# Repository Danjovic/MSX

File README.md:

# MSX
Coletânea de projetos para MSX

1) - Cartucho Caps Lock para Expert, descrito em http://danjovic.blogspot.com/2016/10/cartucho-caps-lock-para-expert.html

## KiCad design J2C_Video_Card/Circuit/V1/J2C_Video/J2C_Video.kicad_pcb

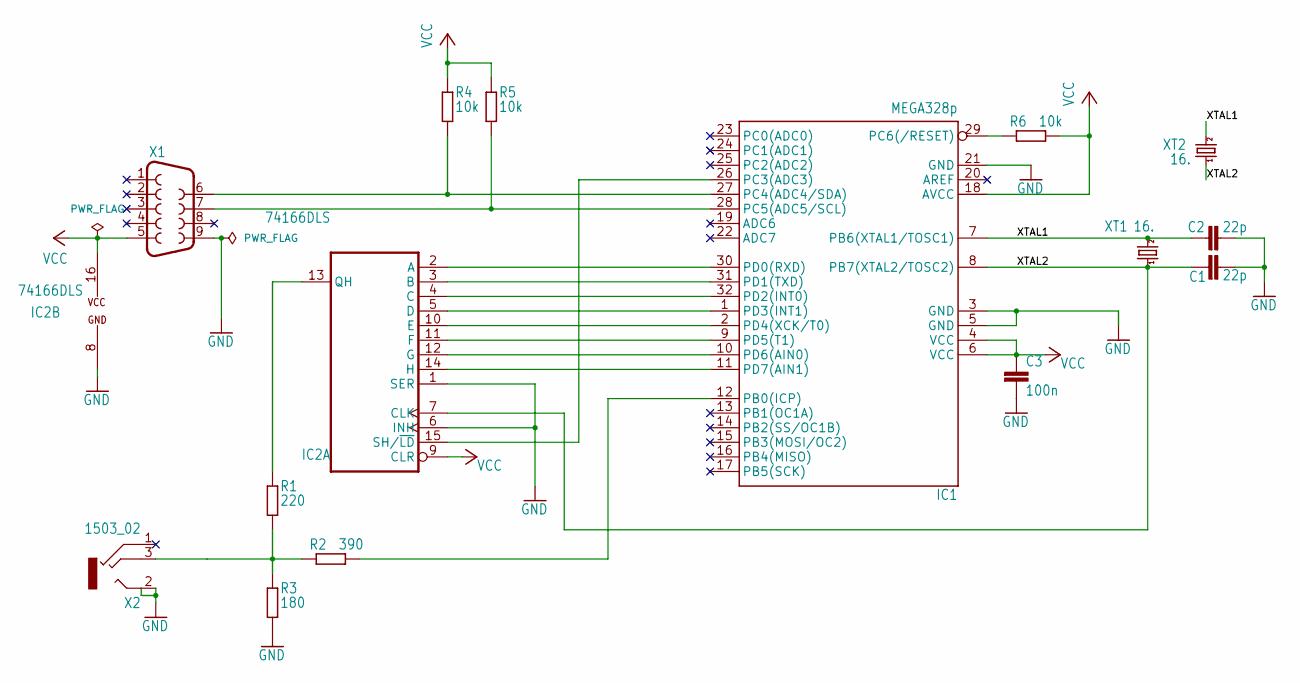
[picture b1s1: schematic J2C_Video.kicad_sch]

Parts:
C1, C2: 22p; C0805
C3: 100n; C0805
IC1: MEGA328p; TQFP32-08; MPN ATMEGA8-16AU
IC2: 74166DLS; SO16
R1: 220; M0805
R2: 390; M0805
R3: 180; M0805
R4, R5, R6: 10k; M0805
X1: F09D
X2: 1503_02
XT1: 16.; TC26V
XT2: 16.; Crystal_HC49-U_Vertical

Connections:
/XTAL1: C2.1, IC1.7 (PB6(XTAL1/TOSC1)), XT1.2, XT2.2
/XTAL2: C1.1, IC1.8 (PB7(XTAL2/TOSC2)), IC2.7 (CLK), XT1.1, XT2.1
GND: C1.2, C2.2, C3.2, IC1.3 (GND), IC1.5 (GND), IC1.21 (GND), IC2.1 (SER), IC2.6 (INH), IC2.8 (GND), R3.2, X1.9, X2.2, X2.2@2 (2)
unnamed: IC1.12 (PB0(ICP)), R2.2
unnamed: IC1.26 (PC3(ADC3)), IC2.15 (SH/~LD)
unnamed: IC1.27 (PC4(ADC4/SDA)), R4.2, X1.6
unnamed: IC1.28 (PC5(ADC5/SCL)), R5.2, X1.7
unnamed: IC1.29 (PC6(/RESET)), R6.1
unnamed: IC1.30 (PD0(RXD)), IC2.2 (A)
unnamed: IC1.31 (PD1(TXD)), IC2.3 (B)
unnamed: IC1.32 (PD2(INT0)), IC2.4 (C)
unnamed: IC1.1 (PD3(INT1)), IC2.5 (D)
unnamed: IC1.2 (PD4(XCK/T0)), IC2.10 (E)
unnamed: IC1.9 (PD5(T1)), IC2.11 (F)
unnamed: IC1.10 (PD6(AIN0)), IC2.12 (G)
unnamed: IC1.11 (PD7(AIN1)), IC2.14 (H)
unnamed: IC2.13 (QH), R1.2
unnamed: R1.1, R2.1, R3.1, X2.3
VCC: C3.1, IC1.4 (VCC), IC1.6 (VCC), IC1.18 (AVCC), IC2.9 (CLR), IC2.16 (VCC), R4.1, R5.1, R6.2, X1.5

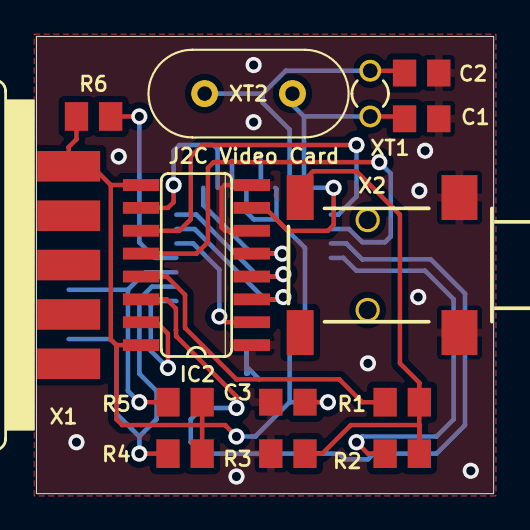
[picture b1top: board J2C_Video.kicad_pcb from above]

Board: 2 copper layers, 25.4 x 25.4 mm, 15 parts (1 on the bottom side), 19 nets.

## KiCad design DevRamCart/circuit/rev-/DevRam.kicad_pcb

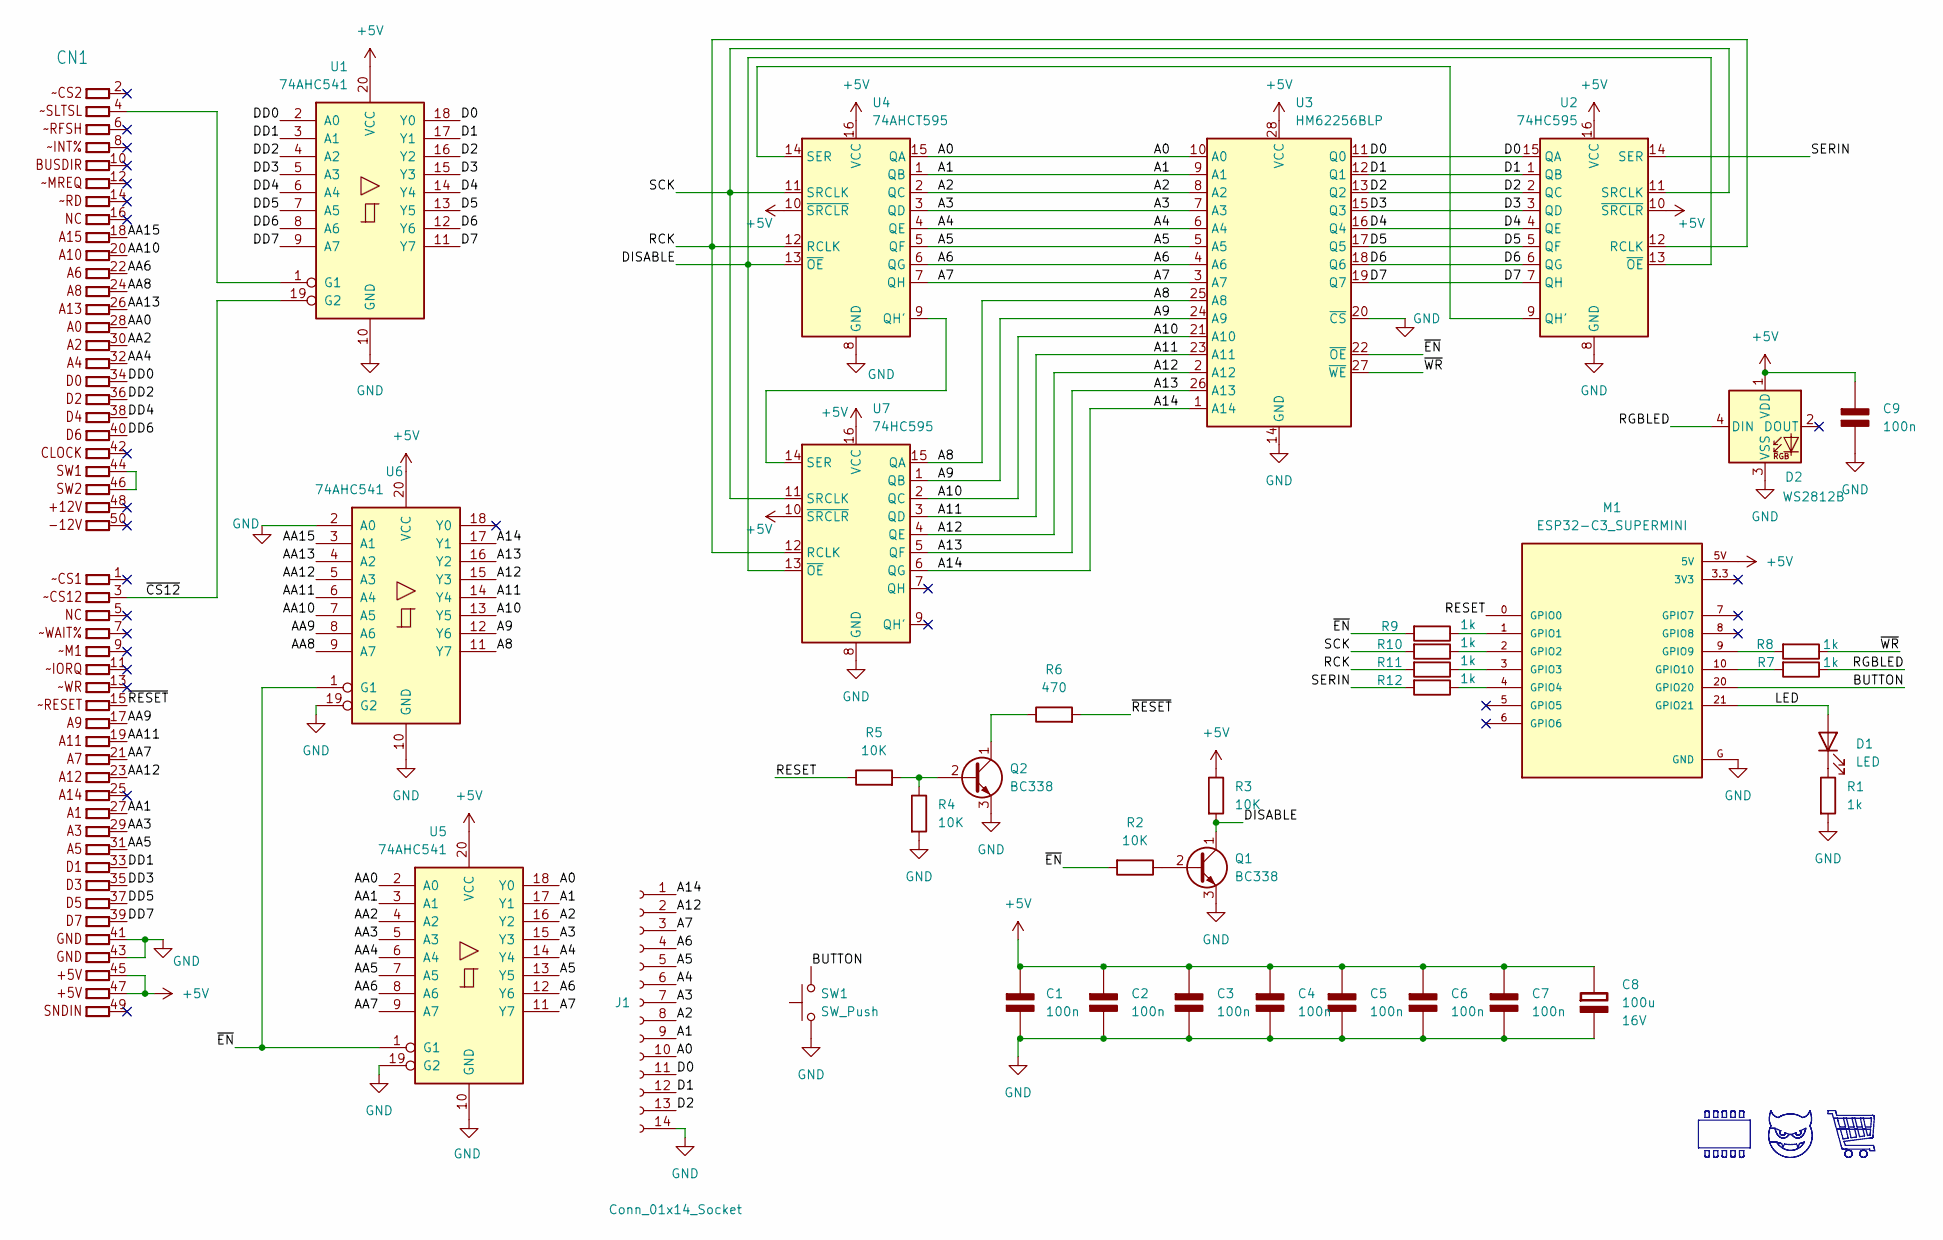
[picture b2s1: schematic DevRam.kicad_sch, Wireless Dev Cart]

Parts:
C1, C2, C3, C4, C5, C6, C7: 100n; C_Disc_D7.5mm_W2.5mm_P5.00mm; Rating V
C8: 100u; CP_Radial_D5.0mm_P2.50mm; Rating 16V
C9: 100n; C_0805_2012Metric; Rating V
CN1: MSXCART
D1: LED; LED_D3.0mm_Horizontal_O1.27mm_Z6.0mm
D2: WS2812B; LED_WS2812B_PLCC4_5.0x5.0mm_P3.2mm
J1: Conn_01x14_Socket; PinHeader_1x14_P2.54mm_Vertical
M1: ESP32-C3_SUPERMINI; MODULE_ESP32-C3_SUPERMINI
Q1, Q2: BC338; TO-92
R1: 1k; R_Axial_DIN0207_L6.3mm_D2.5mm_P7.62mm_Horizontal
R2, R3, R4, R5: 10K; R_Axial_DIN0207_L6.3mm_D2.5mm_P7.62mm_Horizontal
R6: 470; R_Axial_DIN0207_L6.3mm_D2.5mm_P7.62mm_Horizontal
R7, R8, R9, R10, R11, R12: 1k; R_0805_2012Metric
SW1: SW_Push; SW_SPST_Omron_B3F-315x_Angled
U1, U5, U6: 74AHC541; DIP-20_W7.62mm
U2, U7: 74HC595; DIP-16_W7.62mm
U3: HM62256BLP; DIP-28_W7.62mm
U4: 74AHCT595; DIP-16_W7.62mm

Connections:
+5V: C1.1 (+), C2.1 (+), C3.1 (+), C4.1 (+), C5.1 (+), C6.1 (+), C7.1 (+), C8.1 (+), C9.1 (+), CN1.45 (45.+5V), CN1.47 (47.+5V), D2.1 (VDD), M1.5V, R3.1, U1.20 (VCC), U2.10 (~SRCLR), U2.16 (VCC), U3.28 (VCC), U4.10 (~SRCLR), U4.16 (VCC), U5.20 (VCC), U6.20 (VCC), U7.10 (~SRCLR), U7.16 (VCC)
/A0: J1.10, U3.10 (A0), U4.15 (QA), U5.18 (Y0)
/A1: J1.9, U3.9 (A1), U4.1 (QB), U5.17 (Y1)
/A2: J1.8, U3.8 (A2), U4.2 (QC), U5.16 (Y2)
/A3: J1.7, U3.7 (A3), U4.3 (QD), U5.15 (Y3)
/A4: J1.6, U3.6 (A4), U4.4 (QE), U5.14 (Y4)
/A5: J1.5, U3.5 (A5), U4.5 (QF), U5.13 (Y5)
/A6: J1.4, U3.4 (A6), U4.6 (QG), U5.12 (Y6)
/A7: J1.3, U3.3 (A7), U4.7 (QH), U5.11 (Y7)
/A8: U3.25 (A8), U6.11 (Y7), U7.15 (QA)
/A9: U3.24 (A9), U6.12 (Y6), U7.1 (QB)
/A10: U3.21 (A10), U6.13 (Y5), U7.2 (QC)
/A11: U3.23 (A11), U6.14 (Y4), U7.3 (QD)
/A12: J1.2, U3.2 (A12), U6.15 (Y3), U7.4 (QE)
/A13: U3.26 (A13), U6.16 (Y2), U7.5 (QF)
/A14: J1.1, U3.1 (A14), U6.17 (Y1), U7.6 (QG)
/AA0: CN1.28 (28.A0), U5.2 (A0)
/AA1: CN1.27 (27.A1), U5.3 (A1)
/AA2: CN1.30 (30.A2), U5.4 (A2)
/AA3: CN1.29 (29.A3), U5.5 (A3)
/AA4: CN1.32 (32.A4), U5.6 (A4)
/AA5: CN1.31 (31.A5), U5.7 (A5)
/AA6: CN1.22 (22.A6), U5.8 (A6)
/AA7: CN1.21 (21.A7), U5.9 (A7)
/AA8: CN1.24 (24.A8), U6.9 (A7)
/AA9: CN1.17 (17.A9), U6.8 (A6)
/AA10: CN1.20 (20.A10), U6.7 (A5)
/AA11: CN1.19 (19.A11), U6.6 (A4)
/AA12: CN1.23 (23.A12), U6.5 (A3)
/AA13: CN1.26 (26.A13), U6.4 (A2)
/AA15: CN1.18 (18.A15), U6.3 (A1)
/BUTTON: M1.20 (GPIO20), SW1.2
/D0: J1.11, U1.18 (Y0), U2.15 (QA), U3.11 (Q0)
/D1: J1.12, U1.17 (Y1), U2.1 (QB), U3.12 (Q1)
/D2: J1.13, U1.16 (Y2), U2.2 (QC), U3.13 (Q2)
/D3: U1.15 (Y3), U2.3 (QD), U3.15 (Q3)
/D4: U1.14 (Y4), U2.4 (QE), U3.16 (Q4)
/D5: U1.13 (Y5), U2.5 (QF), U3.17 (Q5)
/D6: U1.12 (Y6), U2.6 (QG), U3.18 (Q6)
/D7: U1.11 (Y7), U2.7 (QH), U3.19 (Q7)
/DD0: CN1.34 (34.D0), U1.2 (A0)
/DD1: CN1.33 (33.D1), U1.3 (A1)
/DD2: CN1.36 (36.D2), U1.4 (A2)
/DD3: CN1.35 (35.D3), U1.5 (A3)
/DD4: CN1.38 (38.D4), U1.6 (A4)
/DD5: CN1.37 (37.D5), U1.7 (A5)
/DD6: CN1.40 (40.D6), U1.8 (A6)
/DD7: CN1.39 (39.D7), U1.9 (A7)
/DISABLE: Q1.1 (C), R3.2, U2.13 (~OE), U4.13 (~OE), U7.13 (~OE)
/LED: D1.2 (A), M1.21 (GPIO21)
/RCK: R11.2, U2.12 (RCLK), U4.12 (RCLK), U7.12 (RCLK)
/RESET: M1.0 (GPIO0), R5.1
/RGBLED: D2.4 (DIN), R7.1
/SCK: R10.2, U2.11 (SRCLK), U4.11 (SRCLK), U7.11 (SRCLK)
/SERIN: R12.2, U2.14 (SER)
/~CS12: CN1.3 (3.~CS12), U1.19 (G2)
/~EN: R2.2, R9.2, U3.22 (~OE), U5.1 (G1), U6.1 (G1)
/~RESET: CN1.15 (15.~RESET), R6.2
/~WR: R8.1, U3.27 (~WE)
GND: C1.2 (-), C2.2 (-), C3.2 (-), C4.2 (-), C5.2 (-), C6.2 (-), C7.2 (-), C8.2 (-), C9.2 (-), CN1.41 (41.GND), CN1.43 (43.GND), D2.3 (VSS), J1.14, M1.G (GND), Q1.3 (E), Q2.3 (E), R1.2, R4.2, SW1.1, U1.10 (GND), U2.8 (GND), U3.14 (GND), U3.20 (~CS), U4.8 (GND), U5.10 (GND), U5.19 (G2), U6.2 (A0), U6.10 (GND), U6.19 (G2), U7.8 (GND)
unnamed: CN1.4 (4.~SLTSL), U1.1 (G1)
unnamed: CN1.44 (44.SW1), CN1.46 (46.SW2)
unnamed: D1.1 (K), R1.1
unnamed: Q2.2 (B), R4.1, R5.2
unnamed: Q2.1 (C), R6.1
unnamed: Q1.2 (B), R2.1
unnamed: U4.9 (QH'), U7.14 (SER)
unnamed: U2.9 (QH'), U4.14 (SER)
unnamed: M1.1 (GPIO1), R9.1
unnamed: M1.2 (GPIO2), R10.1
unnamed: M1.3 (GPIO3), R11.1
unnamed: M1.4 (GPIO4), R12.1
unnamed: M1.9 (GPIO9), R8.2
unnamed: M1.10 (GPIO10), R7.2

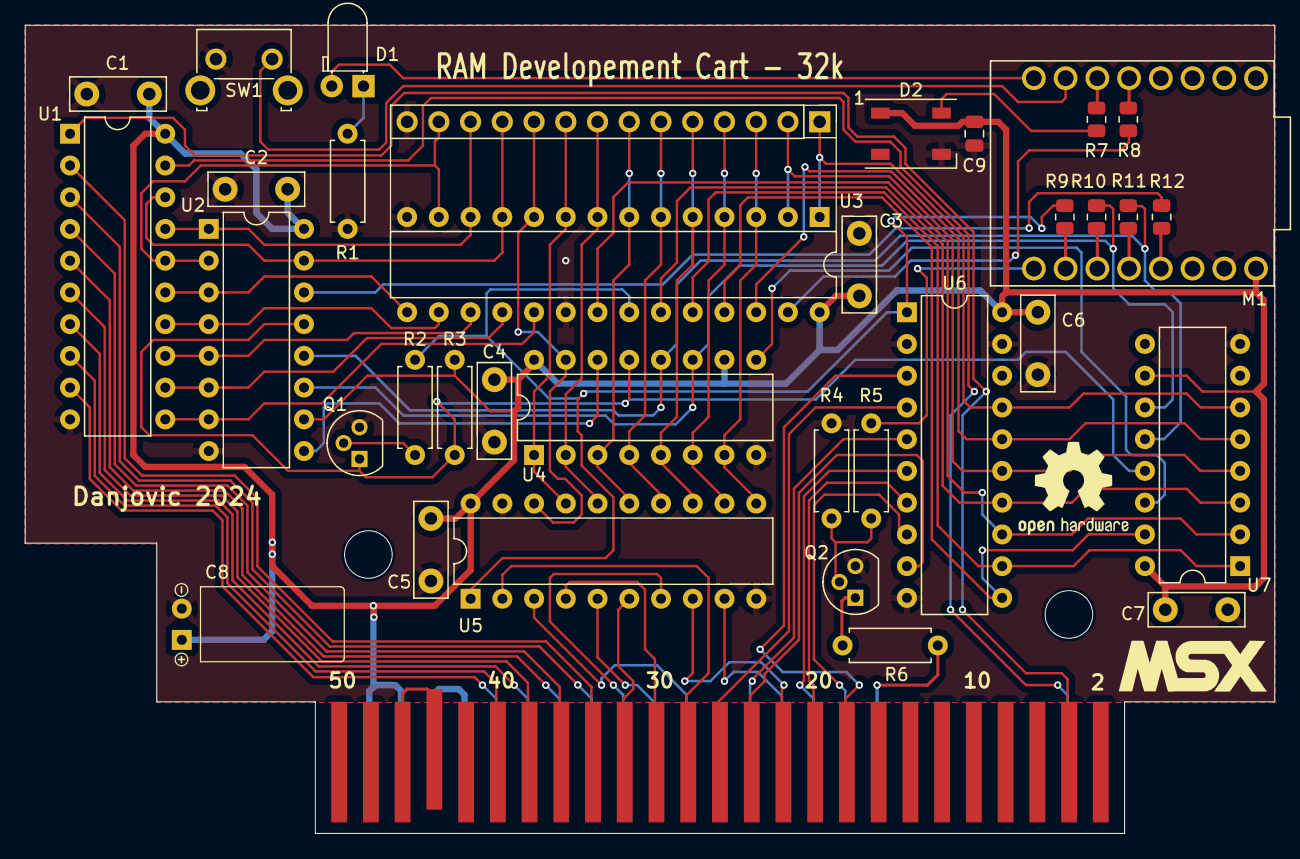
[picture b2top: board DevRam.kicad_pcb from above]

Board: 2 copper layers, 100.0 x 64.7 mm, 36 parts (0 on the bottom side), 74 nets.

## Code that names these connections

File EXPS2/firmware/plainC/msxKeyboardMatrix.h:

//    _____  _____  ___   _____
//   | __\ \/ / _ \/ __| / /_  )
//   | _| >  <|  _/\__ \/ / / /
//   |___/_/\_\_|  |___/_/ /___|
//
//   Teclado PS/2 externo para Expert XP800

// Conexao dos pinos do AVR com a PPI
// AVR interface pin assignment to the PPI

// AVR  PPI

// PC0  PC0   /   sel A
// PC1  PC1   /   sel B
// PC2  PC2   /   sel C
// PC3  PC3   /   sel D

// PD0  PB5   /   X5
// PD1  PB0   /   X0
// PD2  PB6   /   X6
// PD3  PB2   /   X2
// PD4  PB7   /   X7
// PD5  PB4   /   X4
// PD6  PB1   /   X1
// PD7  PB3   /   X3

/*
SH  ROW[0..10] COL [0..7]

    7     6     5     4     3     2     1     0    BIT
 +-----------------------------------------------+
 |SHIFT|       ROW [0..10]     |    COL[0..7]    |
 +-----------------------------------------------+


    7     6     5     4     3     2     1     0    BIT
 +-----------------------------------------------+
 |  7  |  5  |  6  |  4  |  3  |  2  |  1  |  0  |   Row 0
 +-----+-----+-----+-----+-----+-----+-----+-----|
 |  ;  |  [  |  ]  |  \  |  =  |  -  |  9  |  8  |   Row 1
 +-----+-----+-----+-----+-----+-----+-----+-----|
 |  B  |  |  |  A  |  /  |  .  |  ,  |  `  |  '  |   Row 2
 +-----+-----+-----+-----+-----+-----+-----+-----|
 |  J  |  H  |  I  |  G  |  F  |  E  |  D  |  C  |   Row 3
 +-----+-----+-----+-----+-----+-----+-----+-----|
 |  R  |  P  |  Q  |  O  |  N  |  M  |  L  |  K  |   Row 4
 +-----+-----+-----+-----+-----+-----+-----+-----|
 |  Z  |  X  |  Y  |  W  |  V  |  U  |  T  |  S  |   Row 5
 +-----+-----+-----+-----+-----+-----+-----+-----|
 | F3  | F1  | F2  |CODE | CAP |GRAPH|CTRL |SHIFT|   Row 6
 +-----+-----+-----+-----+-----+-----+-----+-----|
 | CR  | BS  | SEL |STOP | TAB | ESC | F5  | F4  |   Row 7
 +-----+-----+-----+-----+-----+-----+-----+-----|
 |RIGHT| UP  |DOWN |LEFT | DEL | INS |HOME |SPACE|   Row 8
 +-----+-----+-----+-----+-----+-----+-----+-----|
 | KP4 | KP2 | KP2 | KP1 | KP0 |NUM/ |NUM+ |NUM* |   Row 9
 +-----+-----+-----+-----+-----+-----+-----+-----|
 |  .  |  -  |  ,  | KP9 | KP8 | KP7 | KP6 | KP5 |   Row 10
 +-----------------------------------------------+
    7     5     6     4     3     2     1     0       Column

*/

// Mapa das linhas de selecao da PPI
// PPI selection line mapping
//      line bit
#define selA  0
#define selB  1
#define selC  2
#define selD  3


#define row0  ( (0<<selD)|(0<<selC)|(0<<selB)|(0<<selA) ) <<3
#define row1  ( (0<<selD)|(0<<selC)|(0<<selB)|(1<<selA) ) <<3
#define row2  ( (0<<selD)|(0<<selC)|(1<<selB)|(0<<selA) ) <<3
#define row3  ( (0<<selD)|(0<<selC)|(1<<selB)|(1<<selA) ) <<3
#define row4  ( (0<<selD)|(1<<selC)|(0<<selB)|(0<<selA) ) <<3
#define row5  ( (0<<selD)|(1<<selC)|(0<<selB)|(1<<selA) ) <<3
#define row6  ( (0<<selD)|(1<<selC)|(1<<selB)|(0<<selA) ) <<3
#define row7  ( (0<<selD)|(1<<selC)|(1<<selB)|(1<<selA) ) <<3
#define row8  ( (1<<selD)|(0<<selC)|(0<<selB)|(0<<selA) ) <<3
#define row9  ( (1<<selD)|(0<<selC)|(0<<selB)|(1<<selA) ) <<3
#define rowA  ( (1<<selD)|(0<<selC)|(1<<selB)|(0<<selA) ) <<3
#define rowB  ( (1<<selD)|(0<<selC)|(1<<selB)|(1<<selA) ) <<3
#define rowC  ( (1<<selD)|(1<<selC)|(0<<selB)|(0<<selA) ) <<3
#define rowD  ( (1<<selD)|(1<<selC)|(0<<selB)|(1<<selA) ) <<3
#define rowE  ( (1<<selD)|(1<<selC)|(1<<selB)|(0<<selA) ) <<3
#define rowF  ( (1<<selD)|(1<<selC)|(1<<selB)|(1<<selA) ) <<3


// Posicao das bits das colunas (teclas)
// Column position bit mapping (keys)
//   column  bit
#define col0  5
#define col1  0
#define col2  6
#define col3  2
#define col4  7
#define col5  4
#define col6  1
#define col7  3


//  SHIFT Position in Matrx
#define LIN_SHIFT 6
#define COL_SHIFT col0


#define _NONE          0x7F
#define _SH            0x80

#define _0            ( row0 | col0 )
#define _1            ( row0 | col1 )
#define _2            ( row0 | col2 )
#define _3            ( row0 | col3 )
#define _4            ( row0 | col4 )
#define _5            ( row0 | col5 )
#define _6            ( row0 | col6 )
#define _7            ( row0 | col7 )

#define _8            ( row1 | col0 )
#define _9            ( row1 | col1 )
#define _MINUS        ( row1 | col2 )
#define _EQUAL        ( row1 | col3 )
#define _OPENBRACKET  ( row1 | col4 )
#define _ACUTE        ( row1 | col5 )
#define _OPENKEY      ( row1 | col6 )
#define _TILDE        ( row1 | col7 )

#define _ASTERISK     ( row2 | col0 )
#define _CCEDIL       ( row2 | col1 )
#define _COMMA        ( row2 | col2 )
#define _DOT          ( row2 | col3 )
#define _SEMICOLON    ( row2 | col4 )
#define _SLASH        ( row2 | col5 )
#define _A            ( row2 | col6 )
#define _B            ( row2 | col7 )

#define _C            ( row3 | col0 )
#define _D            ( row3 | col1 )
#define _E            ( row3 | col2 )
#define _F            ( row3 | col3 )
#define _G            ( row3 | col4 )
#define _H            ( row3 | col5 )
#define _I            ( row3 | col6 )
#define _J            ( row3 | col7 )

#define _K            ( row4 | col0 )
#define _L            ( row4 | col1 )
#define _M            ( row4 | col2 )
#define _N            ( row4 | col3 )
#define _O            ( row4 | col4 )
#define _P            ( row4 | col5 )
#define _Q            ( row4 | col6 )
#define _R            ( row4 | col7 )

#define _S            ( row5 | col0 )
#define _T            ( row5 | col1 )
#define _U            ( row5 | col2 )
#define _V            ( row5 | col3 )
#define _W            ( row5 | col4 )
#define _X            ( row5 | col5 )
#define _Y            ( row5 | col6 )
#define _Z            ( row5 | col7 )

#define _SHIFT        ( row6 | col0 )
#define _CONTROL      ( row6 | col1 )
#define _GRAPH        ( row6 | col2 )
#define _CAPS         ( row6 | col3 )
#define _CODE         ( row6 | col4 )
#define _F1           ( row6 | col5 )
#define _F2           ( row6 | col6 )
#define _F3           ( row6 | col7 )

#define _F4           ( row7 | col0 )
#define _F5           ( row7 | col1 )
#define _ESC          ( row7 | col2 )
#define _TAB          ( row7 | col3 )
#define _STOP         ( row7 | col4 )
#define _BACKSPACE    ( row7 | col5 )
#define _SELECT       ( row7 | col6 )
#define _ENTER        ( row7 | col7 )

#define _SPACE        ( row8 | col0 )
#define _HOME         ( row8 | col1 )
#define _INSERT       ( row8 | col2 )
#define _DELETE       ( row8 | col3 )
#define _LEFT         ( row8 | col4 )
#define _UP           ( row8 | col5 )
#define _DOWN         ( row8 | col6 )
#define _RIGHT        ( row8 | col7 )

#define _KPPLUS       ( row9 | col0 )    
#define _KPMINUS      ( row9 | col1 )    
#define _KPTIMES      ( row9 | col2 )    
#define _KPSLASH      ( row9 | col3 )    

#define _KP1          ( _NONE       )    
#define _KP2          ( _NONE       )    
#define _KP3          ( _NONE       )    
#define _KP4          ( _NONE       )    

#define _KP5          ( _NONE       )    
#define _KP6          ( _NONE       )    
#define _KP7          ( _NONE       )    
#define _KP8          ( _NONE       )   
#define _KP9          ( _NONE       )       
#define _KPCOMMA      ( _NONE       )    
#define _KPDOT        ( _NONE       )    

// Shifted
#define _F6           ( _SH + _F1 )        // F6
#define _F7           ( _SH + _F2 )        // F7
#define _F8           ( _SH + _F3 )        // F8
#define _F9           ( _SH + _F4 )        // F9
#define _F10          ( _SH + _F5 )        // F10

#define _EXCLAMATION  ( _SH + _1  )         // !
#define _QUOTE        ( _SH + _2  )         // "
#define _NUMBER       ( _SH + _3  )         // #
#define _DOLLAR       ( _SH + _4  )         // $
#define _PERCENT      ( _SH + _5  )         // %
#define _POWER        ( _SH + _6  )         // ^
#define _AMPERSAND    ( _SH + _7  )         // &
#define _APOSTROPHE   ( _SH + _8  )         // '
#define _OPENBRACE    ( _SH + _9  )         // (
#define _CLOSEBRACE   ( _SH + _0  )         // )

#define _AT           ( _SH + _ASTERISK   ) // @
#define _UNDERSCORE   ( _SH + _MINUS      ) // _
#define _PLUS         ( _SH + _EQUAL      ) // +
#define _CLOSEKEY     ( _SH + _OPENKEY    ) // }

#define _GRAVE        ( _SH + _ACUTE      ) // `
#define _CLOSEBRACKET ( _SH + _OPENBRACKET) // ]
#define _CIRCUMFLEX   ( _SH + _TILDE      ) // ^

#define _LESSTHAN     ( _SH + _COMMA      ) // <
#define _GREATERTHAN  ( _SH + _DOT        ) // >
#define _COLON        ( _SH + _SEMICOLON  ) // :
#define _QUESTION     ( _SH + _SLASH      ) // ?

#define _PIPE         (  _NONE )

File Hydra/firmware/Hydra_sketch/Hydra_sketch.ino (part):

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
Arduino
/AVR    Function
 0/PD0  Nintendo 64 1 wire Clock/Data
 1/PD1  TXD for serial debug             
 2/PD2  MSX Pulse input (INT0)             
 3/PD3  Dualshock ATT / SNES Latch / Shift Register Latch (Sega) 
 4/PD4  Dualshock CLK / SNES Clock / Shift Register Clock (Sega) 
 5/PD5  Dualshock CMD /            / Sega SELECT    
 6/PD6  Dualshock DATA      
 7/PD7  Dualshock ACK     
 8/PB0  MSX UP    (output)           
 9/PB1  MSX DOWN  (output)             
10/PB2  MSX LEFT  (output)             
11/PB3  MSX RIGHT (output)             
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A0/PC0  Shift Register Data (Sega)   
A1/PC1  SNES Data   
A2/PC2  Mouse DAT           
A3/PC3  Mouse CLK           
A4/PC4  OLED display I2C SCL / WII nunchuck I2C SCL       
A5/PC5  OLED display I2C SDA / WII nunchuck I2C SDA      
*/


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#define mdTRACKBALL         5  // 5 = Trackball
#define mdTOUCHPAD          6  // 6 = Touchpad

#define JoyPin1  8 // PB0 UP
#define JoyPin2  9 // PB1 DOWN
#define JoyPin3 10 // PB2 LEFT
#define JoyPin4 11 // PB3 RIGHT
#define JoyPin6 12 // PB4 TRIGGER A
#define JoyPin7 13 // PB5 TRIGGER B
#define JoyPin8  2 // PD2 PULSE
long time; // No C


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// Nintendo 64 device library by NicoHood
// https://www.github.com/NicoHood/Nintendo
#include "Nintendo.h"
#define N64 0   // PD0
#define GCUBE 7 // PD7
CN64Controller N64Controller(N64);// Define a N64 Controller
CGamecubeController GamecubeController(GCUBE);// Define a Gamecube Controller

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#define MSX_PORT PORTB
#define MSX_DDR  DDRB

#define MSX_UP    0  // PB0
#define MSX_DOWN  1  // PB1
#define MSX_LEFT  2  // PB2
#define MSX_RIGHT 3  // PB3
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
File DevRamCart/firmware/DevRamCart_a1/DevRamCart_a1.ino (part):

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
// GPIO pins / definitions
#define RESET 0    // Active high, resets the MSX
#define nEN 1      // LOW - Enable Z80 Address bus and disable shift registers
#define SCK 2      // Shift register serial clock
#define RCK 3      // Shift register transfer
#define SERIN 4    // Shift register data in first bit A15..A8,A7..A0,D7..D0  last bit
#define nWR 9      // Write pulse for SRAM
#define RGBLED 10  // Neopixel data
#define BUTTON 20  // Button input
#define LED 21     // Red LED

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  pinMode(RESET, OUTPUT);
  pinMode(nEN, OUTPUT);
  pinMode(SCK, OUTPUT);
  pinMode(RCK, OUTPUT);
  pinMode(SERIN, OUTPUT);
  pinMode(nWR, OUTPUT);
  pinMode(RGBLED, OUTPUT);
  pinMode(BUTTON, INPUT_PULLUP);
  pinMode(LED, OUTPUT);

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
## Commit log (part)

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2016-10-28 Basic Release
2016-12-05 Add RESET switch and alternate LED/RESET mounting positons
2016-12-05 wrong name
2016-12-05 Added Reset Button
2016-12-05 useless file
2016-12-05 outdated
2017-12-18 I2C stuff for joystick port
2018-05-16 Repository created
2018-05-22 Added Schematics Folder, added HB8000 schematic redrawn
2018-09-29 J2C code captured from MSX
2019-06-08 Added RF modulator, corrected main board schematic
    Added rebuilt schematics of RF modulator, corrected supply voltage for RF modulator on main board (was 5V instead of 12V) and updated library with LM1889 modulator
2019-06-08 Added RF modulator, updated main board and library
    Added rebuilt schematics of RF modulator, corrected supply voltage for RF modulator on main board (was 5V instead of 12V) and updated library with LM1889 modulator
2019-07-02 added orpheus files
2019-07-02 move files to folder
2019-07-08 upload files - NOT TESTED ON REAL HARDWARE SO FAR
2019-08-11 added N64toMSX subproject
2019-08-12 test version, partially functional
2019-08-12 cleanup
2019-08-12 added project, partially working
2019-08-13 Button logic OK, Autofire not ready yet
2019-08-15 Timeout/task interleaving mechanism behaving as expected
2019-08-18 First NSX-64 working release
2019-08-18 cleanup, conditionals on debug code
2019-08-22 upload of files, not tested!
2019-08-24 Cleanup and organization of some directories
2019-08-24 Added Joystick port Video Card project
2019-09-07 MSX tested working, SMS partially verified.
2020-02-23 Updated component values
2020-03-30 Upload of Files
2020-04-02 Eliminated interference caused by glitches in PULSE line
2020-04-05 Enhanced Version
    Enhanced version, support Arduino UNO, Nano and Digispark, provides both Arkanoid and MSX Standard paddle.
2020-04-05 Added documentation, reorganized directories
2020-04-05 Added Pullup resistor
2020-04-05 Enhanced image
2020-04-05 Enhanded Image
2020-08-07 Added Zorax Logo
2020-08-07 corrected X
2020-11-23 Added Ultimate Caps Lock Reset MSXDOS2 cart PCB Layout
2020-11-23 Corrected Caps Lock LED activation (in LOW)
2020-11-23 Added a buzzer
2020-12-29 Adicionada placa RF Hotbit Preto, contribuição de Fábio Belavenuto.
2021-04-10 Arduino code ported to Plain C
2021-05-23 Updated Single Sided Board
2021-05-30 Corrected PS2 clock/dat pin assignment to reflect PCB
2021-10-20 Added FA-32 cassete adapter schematic
2021-10-20 added schematic in pdf
2021-10-22 Added PCB for Hammond 1593j box
    With two options for transistor and for relay
2021-10-29 Added Cable for board CA3427-3 (FA32 BR version)
2021-10-29 Update board, added images
2021-10-30 Updated files
2021-12-13 very early release
2022-01-02 untested, just uploaded
2022-10-06 added joystick type to return byte in B register
2022-10-07 bug fix
2022-10-10 Adeed DE-9 version, pullup resitors on data lines
2022-10-10 updated schematics
2022-10-11 corrected clock ringing
2022-11-05 Muhonmourn3 patch (untested)
2022-11-06 changed patch start address
2022-11-06 added patch
2022-11-06 changed to use TAP on port 1
2022-11-06 fixed bug tap2 left
2022-11-13 Added ROM version of patched Muhonmourn3
2022-11-15 added splash screen and no-ram screen
2022-11-15 fixed problem with subslots
2023-05-19 Added Touch Digitizer project
2023-12-26 Add files via upload
    upload only, code not debugged
2024-04-02 debugged
2024-11-07 added ScanJ2c
2025-02-26 Added Dev Ram Cart Project
2025-02-27 code cleanup
2025-03-04 Improved Open Collector emulation, fixed compilation with TinyCore
2025-03-29 fixed name of signals on printer port

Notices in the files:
DevRamCart/firmware/DevRamCart_a1/DevRamCart_a1.ino:
Released under GPL V3
Hydra/firmware/Hydra_sketch/Hydra_sketch.ino:
License:GPL V2.0
